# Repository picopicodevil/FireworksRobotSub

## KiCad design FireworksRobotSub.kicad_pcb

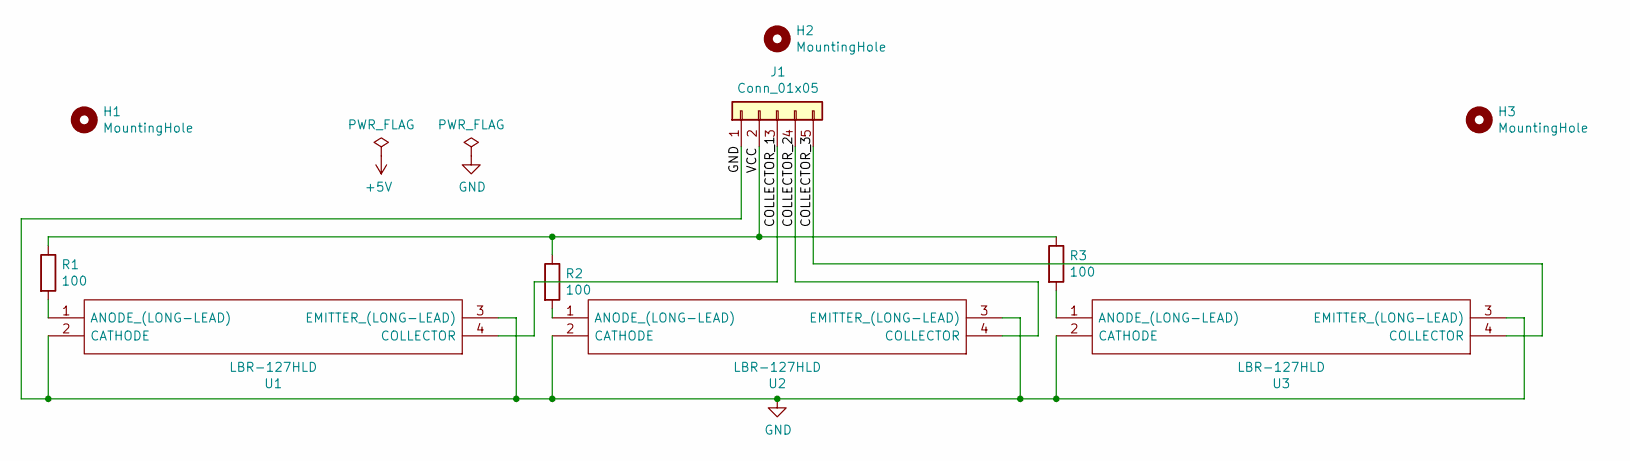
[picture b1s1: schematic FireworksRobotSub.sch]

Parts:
H1, H2, H3: MountingHole; MountingHole_3.2mm_M3
J1: Conn_01x05; PinHeader_1x05_P2.54mm_Vertical
R1, R2, R3: 100; R_0603_1608Metric_Pad1.05x0.95mm_HandSolder
U1, U2, U3: LBR-127HLD; A5131A; Manufacturer_Part_Number LBR-127HLD

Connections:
/COLLECTOR_1: J1.3, U1.4 (COLLECTOR)
/COLLECTOR_2: J1.4, U2.4 (COLLECTOR)
/COLLECTOR_3: J1.5, U3.4 (COLLECTOR)
/VCC: J1.2, R1.1, R2.1, R3.1
GND: J1.1, U1.2 (CATHODE), U1.3 (EMITTER_(LONG-LEAD)), U2.2 (CATHODE), U2.3 (EMITTER_(LONG-LEAD)), U3.2 (CATHODE), U3.3 (EMITTER_(LONG-LEAD))
unnamed: R1.2, U1.1 (ANODE_(LONG-LEAD))
unnamed: R2.2, U2.1 (ANODE_(LONG-LEAD))
unnamed: R3.2, U3.1 (ANODE_(LONG-LEAD))

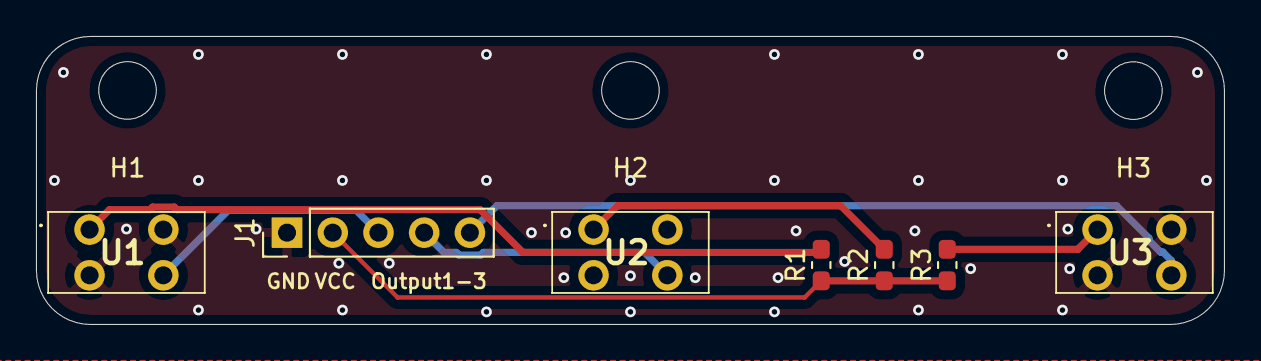
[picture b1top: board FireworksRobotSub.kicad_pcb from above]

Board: 2 copper layers, 66.0 x 16.0 mm, 10 parts (0 on the bottom side), 8 nets.

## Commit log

2020-09-17 order Version 1.0
